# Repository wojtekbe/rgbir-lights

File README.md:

## The concept:

## Parts:
* Power-LEDs:
 - Red: [LZ1-00R102](http://www.ledengin.com/files/products/LZ1/LZ1-00R102.pdf)
 - Green: [LZ1-00G102](http://www.ledengin.com/files/products/LZ1/LZ1-00G102.pdf)
 - Blue: [LZ1-00B202](http://www.ledengin.com/files/products/LZ1/LZ1-00B202.pdf)
 - Infrared: [LZ1-00R602](http://www.ledengin.com/files/products/LZ1/LZ1-00R602.pdf)
 - Cool white: [LZ1-00CW02](http://www.ledengin.com/files/products/LZ1/LZ1-00CW02.pdf)
* Lenses: 24° [FCN10783\_LE1-M](http://www.ledil.com/node/2/p/1688)
* PCA9685 16-channel I2C LED controller
* MBI18001 Power-LED driver

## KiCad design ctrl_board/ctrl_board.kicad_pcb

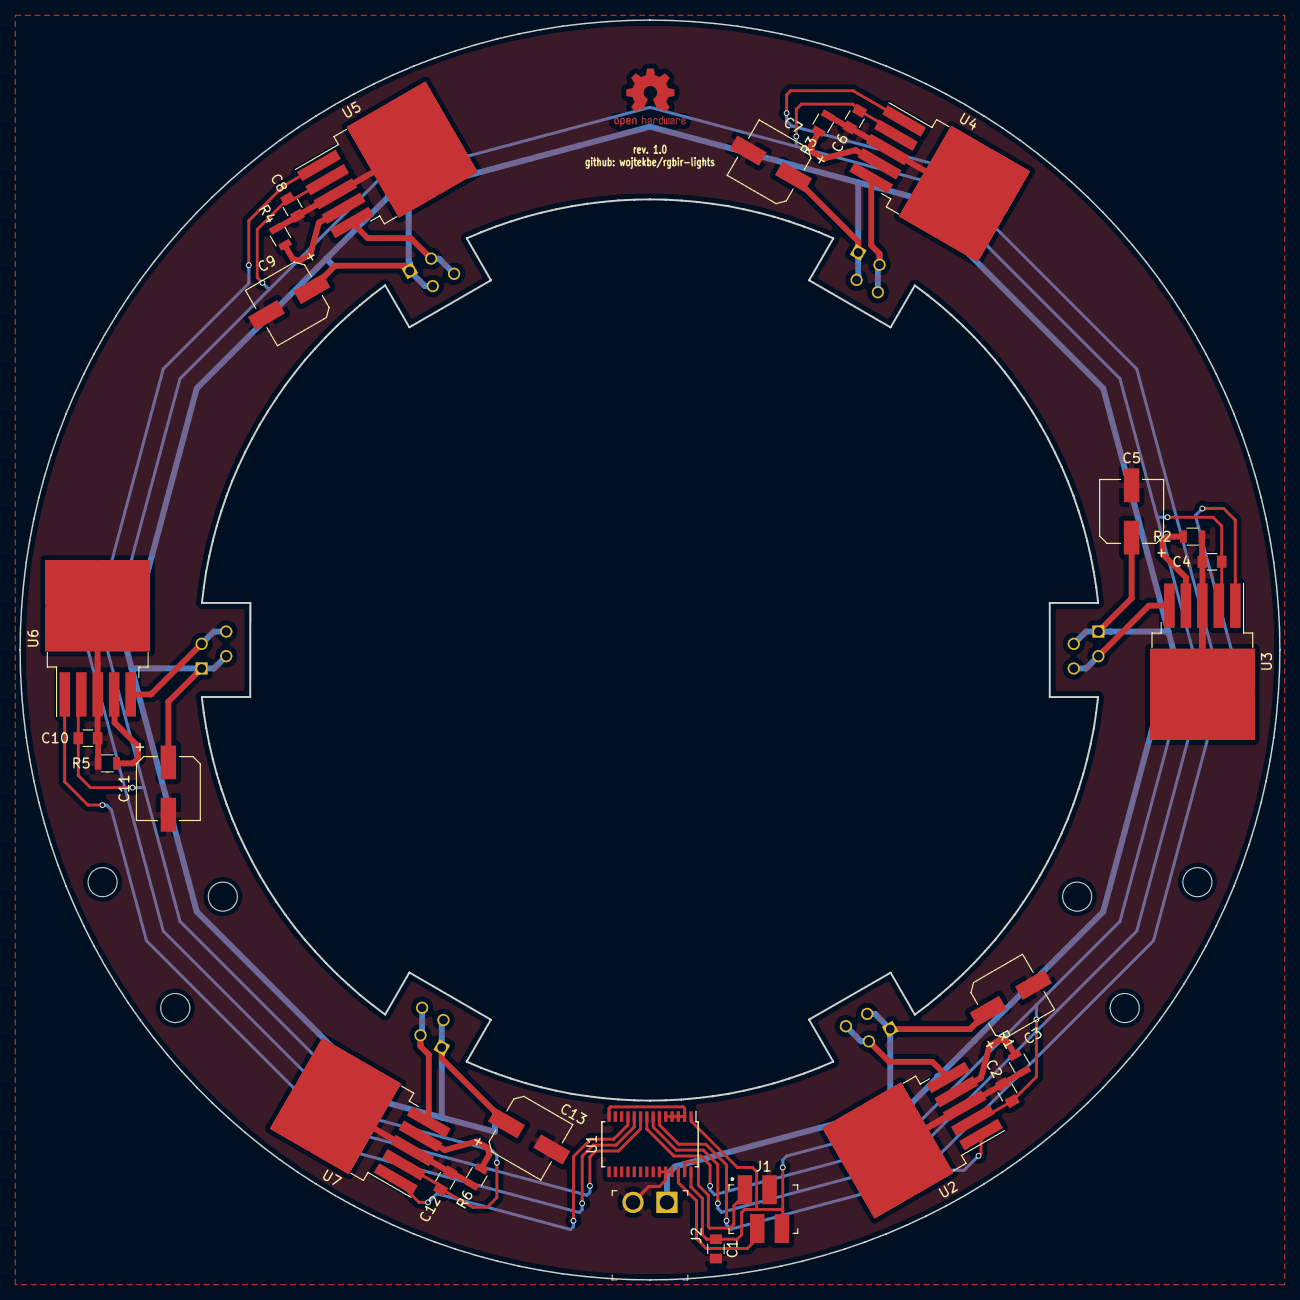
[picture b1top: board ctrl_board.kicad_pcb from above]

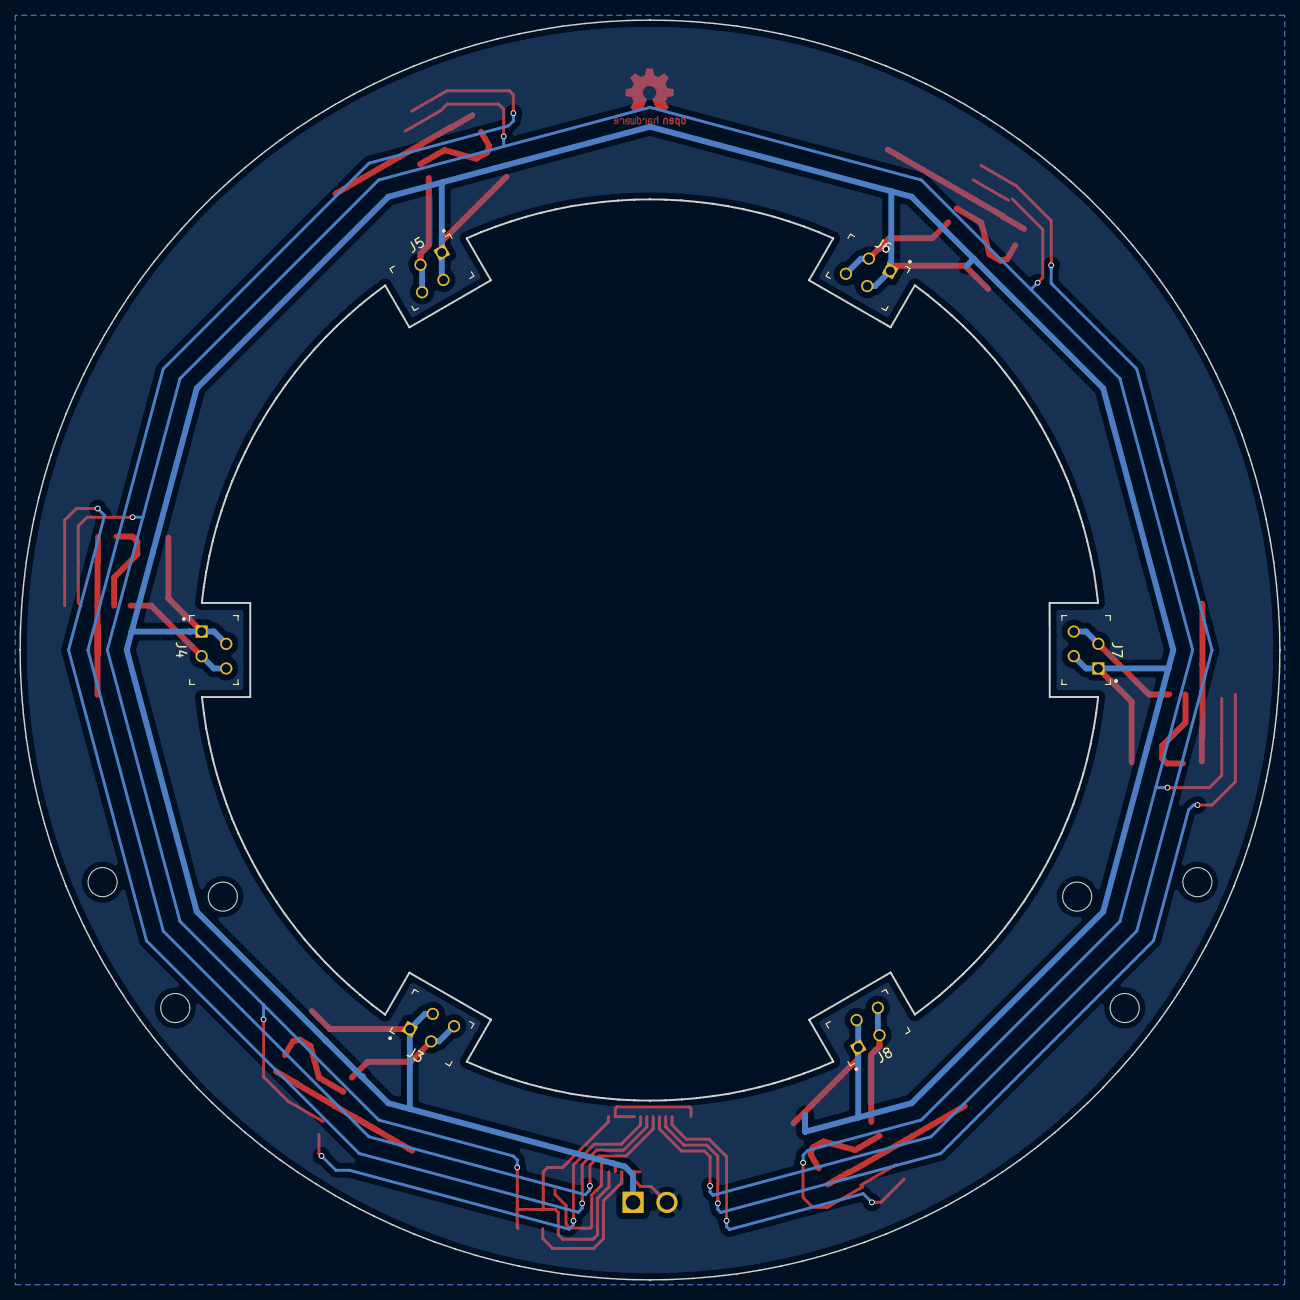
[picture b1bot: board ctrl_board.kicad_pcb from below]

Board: 2 copper layers, 130.0 x 130.0 mm, 35 parts (6 on the bottom side), 23 nets.

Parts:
C1, C2, C4, C6, C8, C10, C12: 100n; C_0805
C3, C5, C7, C9, C11, C13: 100u; CP_Elec_6.3x5.3
G2: LOGO; OSHW_Logo_6mm_height_BCu
J1: CONN_01X04; MicroMatch_4p
J2: CONN_01X02; THT_15EDGRC_2p
J3, J4, J5, J6, J7, J8: CONN_01X04; THT_MicroMatch_4p
R1, R2, R3, R4, R5, R6: 1K; R_0805
U1: PCA9685PW; TSSOP-28_4.4x9.7mm_Pitch0.65mm
U2, U3, U4, U5, U6, U7: MBI1801; TO-263-5_TabPin3

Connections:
+5V: C1.1, C2.1, C4.1, C6.1, C8.1, C10.1, C12.1, J1.4, U1.1, U1.28, U2.2, U3.2, U4.2, U5.2, U6.2, U7.2
CTRL1: U1.6, U2.1
CTRL2: U1.7, U3.1
CTRL3: U1.8, U4.1
CTRL4: U1.9, U5.1
CTRL5: U1.10, U6.1
CTRL6: U1.11, U7.1
GND: C1.2, C2.2, C3.2, C4.2, C5.2, C6.2, C7.2, C8.2, C9.2, C10.2, C11.2, C12.2, C13.2, J1.3, J2.2, R1.2, R2.2, R3.2, R4.2, R5.2, R6.2, U1.2, U1.3, U1.4, U1.5, U1.14, U1.23, U1.24, U1.25, U2.3, U3.3, U4.3, U5.3, U6.3, U7.3
unnamed: J3.3, J3.4, U2.5
unnamed: R1.1, U2.4
unnamed: J4.3, J4.4, U3.5
unnamed: R2.1, U3.4
unnamed: J5.3, J5.4, U4.5
unnamed: R3.1, U4.4
unnamed: J6.3, J6.4, U5.5
unnamed: R4.1, U5.4
unnamed: J7.3, J7.4, U6.5
unnamed: R5.1, U6.4
unnamed: J8.3, J8.4, U7.5
unnamed: R6.1, U7.4
SCL: J1.2, U1.26
SDA: J1.1, U1.27
VLED: C3.1, C5.1, C7.1, C9.1, C11.1, C13.1, J2.1, J3.1, J3.2, J4.1, J4.2, J5.1, J5.2, J6.1, J6.2, J7.1, J7.2, J8.1, J8.2

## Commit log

2017-03-31 add README.md
2017-03-31 add .gitignore
2017-03-31 add initial PCB project
2017-04-04 pcb: add Makefile (netlist)
2017-04-04 pcb: add macroblock library
2017-04-05 fix passing KISYSMOD
2017-04-06 libs to pcb/lib/, use skidl from repo
2017-04-06 ignoring *.log files
2017-04-06 schematic.py -> lights.py
2017-04-07 Makefile: schematic.py -> lights.py
2017-04-07 pcb: add macroblock lib description file
2017-04-08 pcb: add and connect elements [wip]
2017-04-08 pcb: add initial board design
2017-04-09 pcb: change vled conn footprint
2017-04-09 add LED board initial concept
2017-04-09 pcb/ -> control_board/
2017-04-12 control_brd: use external libs in skidl fmt
2017-04-12 control_brd: update PCB design
2017-04-12 add micromatch connector footprint
2017-04-12 control_brd: add micromatch connector for each LED driver
2017-04-12 Connectors_micromatch: add VAL**
2017-04-21 Connectors_micromatch.pretty -> Connectors_wb.pretty
2017-04-21 footprints: THT_4P: change outline
2017-04-22 control_brd: add 6-pin 2mm header
2017-04-22 control_brd: Makefile cleanup
2017-04-22 control_brd: netlist: add main_connector
2017-04-23 control_brd: rename files
2017-04-23 control_board: add automatically generated footprints
2017-04-23 ctrl_brd: change main_connector
2017-04-23 footprints.py: cleanup
2017-04-28 Ignore generated.pretty lib
2017-04-28 Move SKiDL subcircuits to separate file
2017-04-28 Ignore *.pyc
2017-04-28 generated.pretty: Add Jetson TK1 expansion connector
2017-05-05 Add concept design and rendered image
2017-05-07 ctrl_board: change main connecotr footprint
2017-05-07 control_board: swap anode/cathode in output connector
2017-05-07 Initial pcbnew helper scripts
2017-05-07 ctrl_board: [wip] place and route
2017-05-12 ki_scripts: some new funcs
2017-05-17 ki_scripts: track arc
2017-05-28 ki_scripts: graphics: polyline, arc
2017-05-28 Remove Connectors_wb lib
2017-05-28 ctrl_board: Open Hardware logo
2017-05-28 ki_scripts: simple circle pattern
2017-05-28 Ignore backup files
2017-05-29 control_board: pca9685: fix i2c addr
2017-05-30 Drop Makefile
2017-05-30 .gitignore: ignore *_lib_sklib.py
2017-06-02 Fix micromatch footprint, add tripod mount footprint
2017-06-02 update helpers script
2017-06-05 ctrl_board: tripod mount: drill = 3mm
2017-06-16 ki_sripts: generate BOM
2017-06-16 control_board: caps' value 100u
2017-06-16 ctrl_board: generate gerber files
2017-06-16 Add control board PCB design to README
2017-10-09 ctrl_board: fixes: PCA9685, MBI1801 package
2017-10-09 control board: rev1.1: place and route
2018-05-11 move foontprints to libs/
2018-05-11 add mcpcb board project
2018-05-11 gitignore: ignore gerber files
2018-05-11 Update README (remove pcb design images)
2018-05-11 libs: add LZ1 footprint
2018-05-11 control_board: rename folder to ctrl_board
2018-05-11 mcpcb: routing
2018-05-14 libs: powerled: add unmodified LZ1 footprint
2018-05-14 mcpcb: update layout, add filled zone
